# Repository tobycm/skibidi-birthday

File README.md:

# skibidi-birthday

Happy birthday [Kai](https://github.com/KaiPereira)!! I wanted to put some FPGA footprint stuff but its too advanced for me lol. Hope you enjoy this card gift.

This is a USB 2.0 Hub, it doesn't need to have a case because the pcb itself is a birthday card, having a case would obviously hides the decorations and art on the pcb so it makes sense to not have a case designed.

[\[Blueprint\]](https://blueprint.hackclub.com/projects/13659) | [\[KiCanvas\]](https://kicanvas.org/?repo=https%3A%2F%2Fgithub.com%2Ftobycm%2Fskibidi-birthday%2Ftree%2Fmain%2Fpcb)

## PCB

2-Layer PCB, ENIG finish and white color with black silkscreen

## Schematic

# BOM

BOM is optimized for LCSC to help remove handling fee

| Description | Quantity | Part # | Unit Price | Extended Price (USD) | Product Link |
| :--- | :---: | :--- | :---: | :---: | :--- |
| 100nF ±10% 50V Ceramic Capacitor X7R 0603 | 100 | CL10B104KB8NNNC | 0.0028 | 0.28 | [Link](https://www.lcsc.com/product-detail/C1591.html) |
| 18.6VC Clamp 9.4A@8/20us Ipp ESD DIODE SOD-523 | 20 | ESD5Z5.0T1G | 0.0354 | 0.71 | [Link](https://www.lcsc.com/product-detail/C82044.html) |
| Polymeric PTC Resettable Fuse 12V 2A Surface Mount 1206 | 10 | BSMD1206-200-12V | 0.0616 | 0.62 | [Link](https://www.lcsc.com/product-detail/C883135.html) |
| 220Ω@100MHz 1 Line Ferrite Bead 0805 2A 45mΩ | 50 | BLM21PG221SN1D | 0.0229 | 1.15 | [Link](https://www.lcsc.com/product-detail/C85840.html) |
| USB-C (USB TYPE-C) Receptacle Connector 16 Position Surface Mount | 25 | TYPE-C-31-M-14 | 0.3534 | 8.84 | [Link](https://www.lcsc.com/product-detail/C223907.html) |
| 5.1kΩ ±1% 100mW 0603 Thick Film Resistor | 100 | FRC0603F5101TS | 0.0012 | 0.12 | [Link](https://www.lcsc.com/product-detail/C2907044.html) |
| 56kΩ ±1% 100mW 0603 Thick Film Resistor | 100 | 0603WAF5602T5E | 0.0013 | 0.13 | [Link](https://www.lcsc.com/product-detail/C23206.html) |
| 4 480Mbps USB 2.0 Hub QFN-16(3x3) Interface Controllers | 6 | CH334P | 0.4538 | 2.72 | [Link](https://www.lcsc.com/product-detail/C5373042.html) |
| 12VC Clamp 4.5A Ipp ESD DIODE SOT-23-6L | 40 | USBLC6-4SC6-ES | 0.0216 | 0.86 | [Link](https://www.lcsc.com/product-detail/C5180279.html) |
| **LCSC Shipping** | 1 | LCSC Shipping | 26.06 | 26.06 | [Link](https://www.lcsc.com/) |
| **2-Layer PCB** | 5 | PCB | 3.80 | 19.00 | [Link](https://jlcpcb.com/) |
| **Stencil** | 1 | Stencil | 3.05 | 3.05 | [Link](https://jlcpcb.com/) |
| **JLCPCB Shipping** | 1 | JLCPCB Shipping | 9.69 | 9.69 | [Link](https://jlcpcb.com/) |
| --- | --- | --- | --- | --- | --- |
| **Total** | | | | **$73.22** | |

 <a href="https://github.com/tobycm">tobycm</a>

This project was funded by [Blueprint](https://blueprint.hackclub.com/), a grant program by Hack Club that supports open source hardware projects for teenagers.

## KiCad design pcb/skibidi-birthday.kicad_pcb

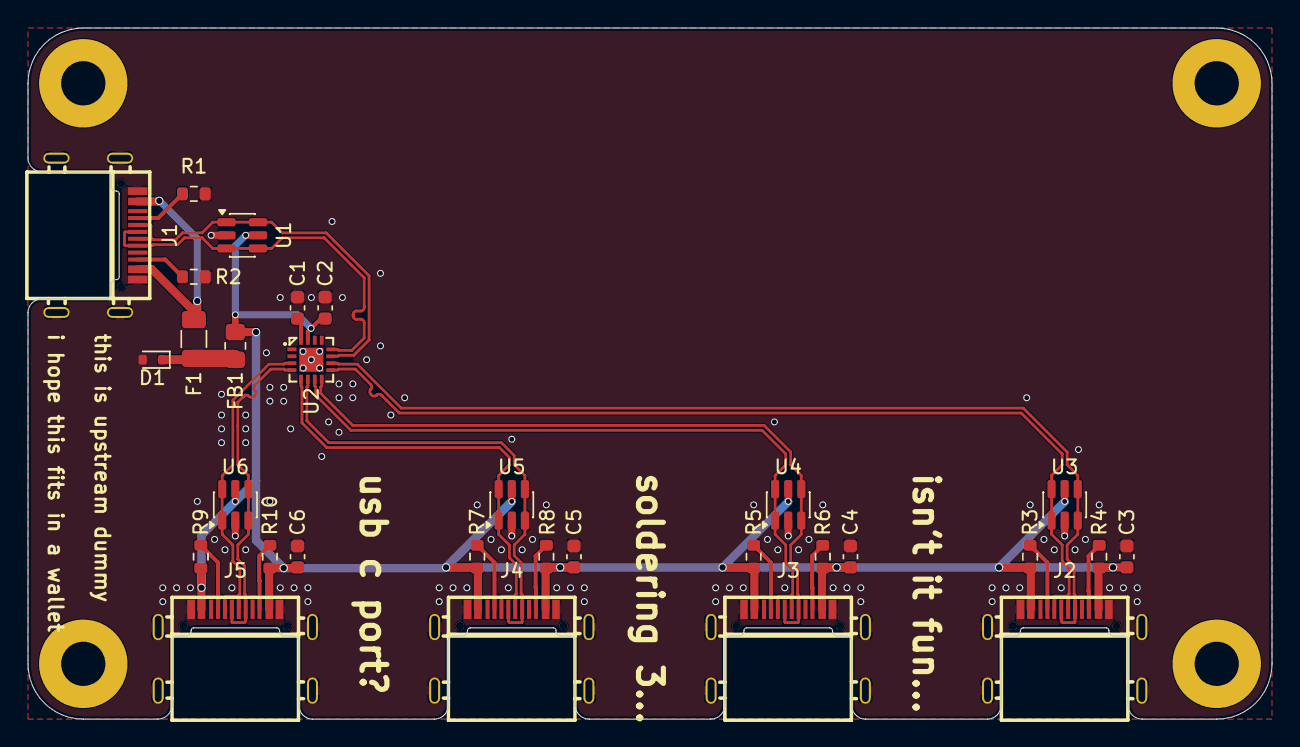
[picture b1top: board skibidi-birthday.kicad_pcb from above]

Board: 2 copper layers, 90.0 x 50.0 mm, 34 parts (0 on the bottom side), 25 nets.

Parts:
C1, C2: 100n; C_0603_1608Metric
C3, C4, C5, C6: 10u; C_0603_1608Metric
D1: 5V; D_SOD-523
F1: 2A; Fuse_1206_3216Metric
FB1: 220Ω@100MHz; R_0805_2012Metric_Pad1.20x1.40mm_HandSolder
H1, H2, H3, H4: MountingHole; MountingHole_3.2mm_M3_Pad
J1, J2, J3, J4, J5: USB_C_Receptacle_USB2.0_16P; USB-C-SMD_12P-P0.50-H-F_TYPE-C-31-M-14
R1, R2: 5.1k; R_0603_1608Metric
R3, R4, R5, R6, R7, R8, R9, R10: 56k; R_0603_1608Metric
U1, U3, U4, U5, U6: USBLC6-2SC6; SOT-23-6
U2: CH334P; QFN-16_L3.0-W3.0-P0.50-BL-EP1.7

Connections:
/1D+: J2.A6 (D+), J2.B6 (D+), U2.10 (DP1), U3.3 (I/O2), U3.4 (I/O2)
/1D-: J2.A7 (D-), J2.B7 (D-), U2.9 (DM1), U3.1 (I/O1), U3.6 (I/O1)
/2D+: J3.A6 (D+), J3.B6 (D+), U2.8 (DP2), U4.3 (I/O2), U4.4 (I/O2)
/2D-: J3.A7 (D-), J3.B7 (D-), U2.7 (DM2), U4.1 (I/O1), U4.6 (I/O1)
/3D+: J4.A6 (D+), J4.B6 (D+), U2.6 (DP3), U5.3 (I/O2), U5.4 (I/O2)
/3D-: J4.A7 (D-), J4.B7 (D-), U2.5 (DM3), U5.1 (I/O1), U5.6 (I/O1)
/4D+: J5.A6 (D+), J5.B6 (D+), U2.4 (DP4), U6.3 (I/O2), U6.4 (I/O2)
/4D-: J5.A7 (D-), J5.B7 (D-), U2.3 (DM4), U6.1 (I/O1), U6.6 (I/O1)
/UD+: J1.A6 (D+), J1.B6 (D+), U1.3 (I/O2), U1.4 (I/O2), U2.12 (DPU)
/UD-: J1.A7 (D-), J1.B7 (D-), U1.1 (I/O1), U1.6 (I/O1), U2.11 (DMU)
GND: C1.2, C2.1, C3.2, C4.2, C5.2, C6.2, D1.2 (A2), J1.A1 (GND), J1.B1 (GND), J1.S1 (SHIELD), J2.A1 (GND), J2.B1 (GND), J2.S1 (SHIELD), J3.A1 (GND), J3.B1 (GND), J3.S1 (SHIELD), J4.A1 (GND), J4.B1 (GND), J4.S1 (SHIELD), J5.A1 (GND), J5.B1 (GND), J5.S1 (SHIELD), R1.2, R2.2, U1.2 (GND), U2.17 (GND), U3.2 (GND), U4.2 (GND), U5.2 (GND), U6.2 (GND)
unnamed: D1.1 (A1), F1.2, FB1.1
unnamed: F1.1, J1.A4 (VBUS), J1.B4 (VBUS)
unnamed: J1.A5 (CC1), R1.1
unnamed: J1.B5 (CC2), R2.1
unnamed: J2.A5 (CC1), R3.2
unnamed: J2.B5 (CC2), R4.2
unnamed: J3.A5 (CC1), R5.2
unnamed: J3.B5 (CC2), R6.2
unnamed: J4.A5 (CC1), R7.2
unnamed: J4.B5 (CC2), R8.2
unnamed: J5.A5 (CC1), R9.2
unnamed: J5.B5 (CC2), R10.2
unnamed: C1.1, U2.16 (VDD33)
VBUS: C2.2, C3.1, C4.1, C5.1, C6.1, FB1.2, J2.A4 (VBUS), J2.B4 (VBUS), J3.A4 (VBUS), J3.B4 (VBUS), J4.A4 (VBUS), J4.B4 (VBUS), J5.A4 (VBUS), J5.B4 (VBUS), R3.1, R4.1, R5.1, R6.1, R7.1, R8.1, R9.1, R10.1, U1.5 (VBUS), U2.15 (V5), U3.5 (VBUS), U4.5 (VBUS), U5.5 (VBUS), U6.5 (VBUS)

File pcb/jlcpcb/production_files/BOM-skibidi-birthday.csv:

Comment,Designator,Footprint,LCSC,Quantity
100n,"C1,C2",C_0603_1608Metric,C1591,2
10u,"C3,C4,C5,C6",C_0603_1608Metric,C96446,4
220Ω@100MHz,FB1,R_0805_2012Metric_Pad1.20x1.40mm_HandSolder,C85840,1
2A,F1,Fuse_1206_3216Metric,C883135,1
5.1k,"R1,R2",R_0603_1608Metric,C2907044,2
56k,"R10,R3,R4,R5,R6,R7,R8,R9",R_0603_1608Metric,C23206,8
5V,D1,D_SOD-523,C82044,1
CH334P,U2,QFN-16_L3.0-W3.0-P0.50-BL-EP1.7,C5373042,1
USBLC6-2SC6,"U1,U3,U4,U5,U6",SOT-23-6,C2827654,5
USB_C_Receptacle_USB2.0_16P,"J1,J2,J3,J4,J5",USB-C-SMD_12P-P0.50-H-F_TYPE-C-31-M-14,C223907,5

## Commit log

2026-03-31 forgor to commit... so here's a big one
2026-03-31 Update KiCanvas link
2026-03-31 add bom
2026-03-31 forgot to length match for the 67th time
2026-04-25 update bom and cpl
